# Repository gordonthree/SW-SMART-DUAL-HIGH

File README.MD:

# Dual High Side Smart Switch Node
* STM32G071 Microcontroller on board
* Dual BTS7002 Profet Smart Switches for high side loads, rated at 20 amps
* Microchip MCP2562 isolated CAN bus transceiver
* Voltage divider to monitor supply voltage
* Switch current monitoring and diagnostics
* Three position screw terminal block for CAN bus connection
* Three pos. screw terminal block for power-out, middle terminal is NC
* Heavy duty terminal block connectors for power in
* Headers for SWLINK programming and USART1 debug serial port

<IMG src="https://github.com/gordonthree/SW-SMART-DUAL-HIGH/blob/main/SW-SMART-DUAL-HIGH.png?raw=true" width=480>

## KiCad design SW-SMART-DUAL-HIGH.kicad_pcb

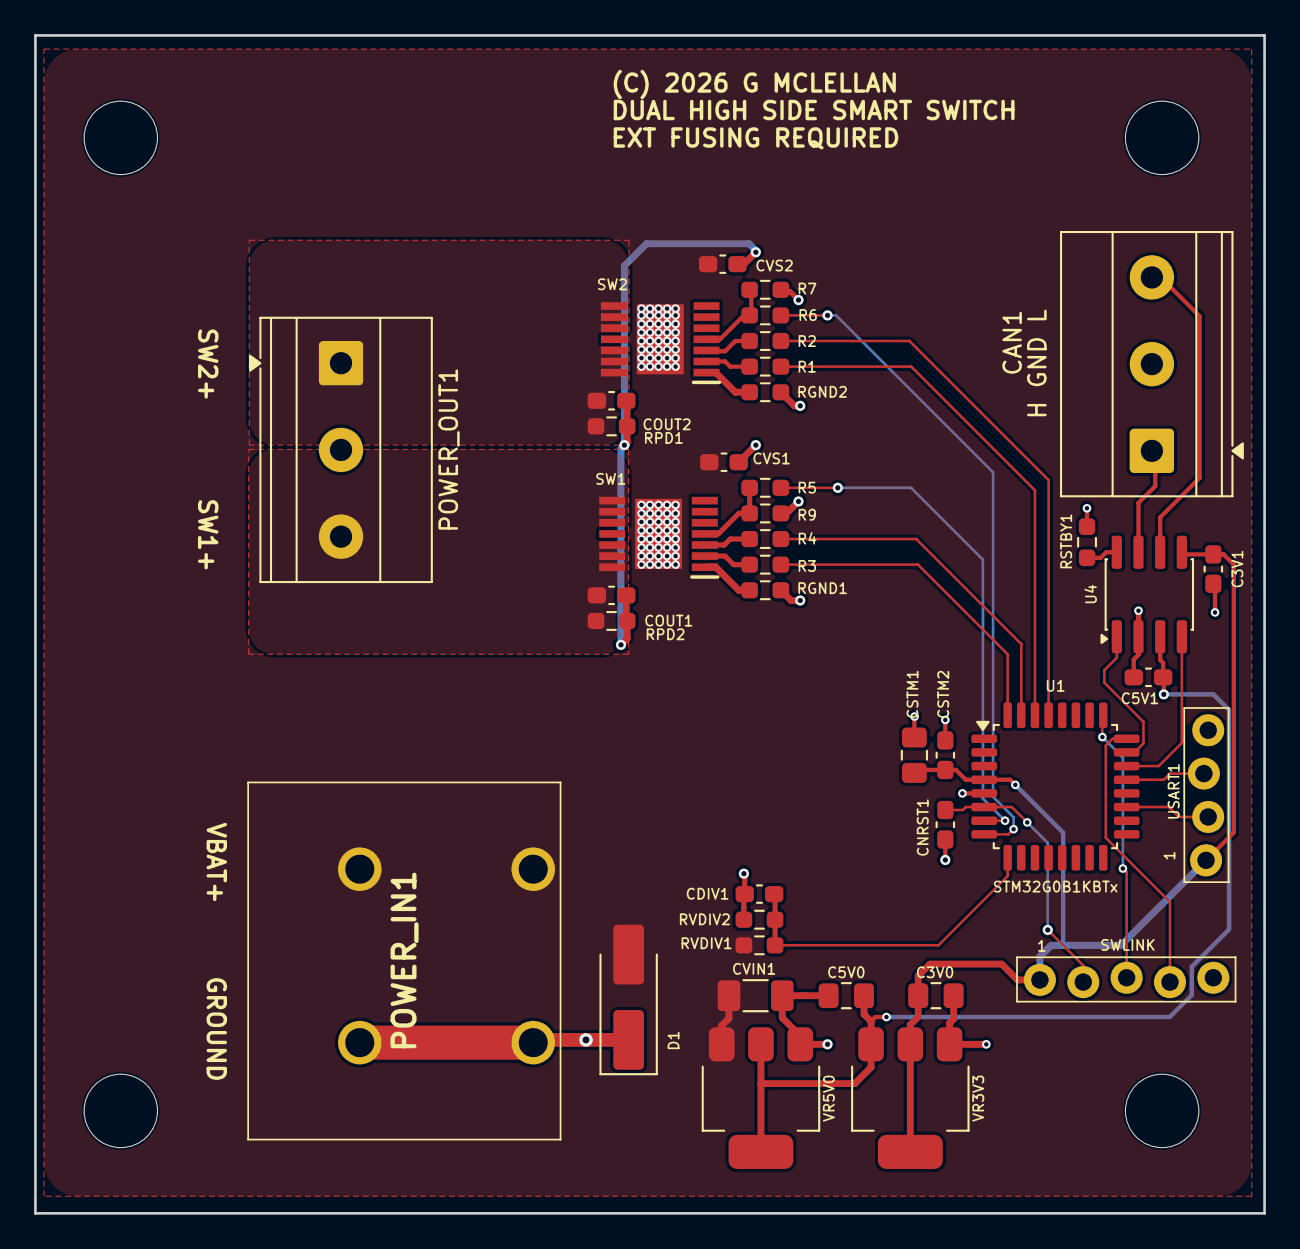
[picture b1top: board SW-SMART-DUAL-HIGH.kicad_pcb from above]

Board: 2 copper layers, 72.0 x 69.0 mm, 44 parts (0 on the bottom side), 31 nets.

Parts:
C3V0, C5V0: 10u; C_0805_2012Metric_Pad1.18x1.45mm_HandSolder
C3V1, C5V1: 100n; C_0603_1608Metric_Pad1.08x0.95mm_HandSolder
CAN1: H GND L; TerminalBlock_Phoenix_MKDS-1,5-3-5.08_1x03_P5.08mm_Horizont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
CDIV1: 100n; C_0603_1608Metric_Pad1.08x0.95mm_HandSolder
CNRST1: 100n; C_0603_1608Metric_Pad1.08x0.95mm_HandSolder
COUT1, COUT2: 10n; C_0603_1608Metric_Pad1.08x0.95mm_HandSolder
CSTM1: 4u7; C_0805_2012Metric_Pad1.18x1.45mm_HandSolder
CSTM2: 100n; C_0603_1608Metric_Pad1.08x0.95mm_HandSolder
CVIN1: 10u; C_1206_3216Metric_Pad1.33x1.80mm_HandSolder
CVS1, CVS2: 68n; C_0603_1608Metric_Pad1.08x0.95mm_HandSolder
D1: 33V; D_SMA_Handsoldering
H1, H2, H3, H4: M4 4.3mm; MountingHole_4.3mm_M4
J1: SWLINK; 1x05_P2.54mm_Locking
J2: USART1; 1x04_P2.54mm_Locking
POWER_IN1: PWRIN; VP0265840000G
POWER_OUT1: TerminalBlock_Phoenix_MKDS-1,5-3-5.08_1x03_P5.08mm_Horizont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
R1, R2, R3, R4: 4K7; R_0603_1608Metric_Pad0.98x0.95mm_HandSolder
R5, R6: 10K; R_0603_1608Metric_Pad0.98x0.95mm_HandSolder
R7, R9: 1K0; R_0603_1608Metric_Pad0.98x0.95mm_HandSolder
RGND1, RGND2: 47R; R_0603_1608Metric_Pad0.98x0.95mm_HandSolder
RPD1, RPD2: 47K; R_0603_1608Metric_Pad0.98x0.95mm_HandSolder
RSTBY1: 10K; R_0603_1608Metric_Pad0.98x0.95mm_HandSolder
RVDIV1: 4K7; R_0603_1608Metric_Pad0.98x0.95mm_HandSolder
RVDIV2: 1K0; R_0603_1608Metric_Pad0.98x0.95mm_HandSolder
SW1, SW2: BTS7002-1EPP; SOP65P600X115-15N
U1: STM32G0B1KBTx; LQFP-32_7x7mm_P0.8mm
U4: MCP2562-E-SN; SOIC-8_3.9x4.9mm_P1.27mm
VR3V3: NCV1117ST33; SOT-223-3_TabPin2
VR5V0: NCV1117ST50; SOT-223-3_TabPin2

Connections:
+3.3V: C3V0.1, C3V1.1, CSTM1.1, CSTM2.1, J1.1, J2.1, U1.4 (VDD), U4.5 (Vio), VR3V3.2 (VO)
+5V: C5V0.1, C5V1.1, U4.3 (VDD), VR3V3.3 (VI), VR5V0.2 (VO)
+12V: CVIN1.1, CVS1.1, CVS2.1, D1.2 (A2), POWER_IN1.1, POWER_IN1.2, RVDIV1.2, SW1.15 (VS), SW2.15 (VS), VR5V0.3 (VI)
/CAN1_RX: U1.22 (PA9/PA11), U4.4 (RXD)
/CAN1_TX: U1.23 (PA10/PA12), U4.1 (TXD)
/CAN_H: CAN1.1, U4.7 (CANH)
/CAN_L: CAN1.3, U4.6 (CANL)
/NRST: CNRST1.1, J1.2, U1.6 (PF2)
/SW1DEN: R4.1, U1.31 (PB7)
/SW1IN: R3.1, U1.32 (PB8)
/SW1IS: R5.1, U1.7 (PA0)
/SW1IS_PD: R5.2, R9.2, SW1.4 (IS)
/SW1OUT: COUT1.1, POWER_OUT1.3, RPD2.2, SW1.8 (OUT), SW1.9 (OUT), SW1.10 (OUT), SW1.12 (OUT), SW1.13 (OUT), SW1.14 (OUT)
/SW2DEN: R2.1, U1.29 (PB5)
/SW2IN: R1.1, U1.30 (PB6)
/SW2IS: R6.1, U1.8 (PA1)
/SW2IS_PD: R6.2, R7.2, SW2.4 (IS)
/SW2OUT: COUT2.1, POWER_OUT1.1, RPD1.2, SW2.8 (OUT), SW2.9 (OUT), SW2.10 (OUT), SW2.12 (OUT), SW2.13 (OUT), SW2.14 (OUT)
/SWCLK: J1.3, U1.25 (PA14)
/SWDIO: J1.4, U1.24 (PA13)
/USART1_RX: J2.3, U1.21 (PA10/UCPD1_DBCC2)
/USART1_TX: J2.2, U1.19 (PA9/UCPD1_DBCC1)
/VS: CDIV1.1, RVDIV1.1, RVDIV2.2, U1.9 (PA2)
GND: C3V0.2, C3V1.2, C5V0.2, C5V1.2, CAN1.2, CDIV1.2, CNRST1.2, COUT1.2, COUT2.2, CSTM1.2, CSTM2.2, CVIN1.2, CVS1.2, CVS2.2, D1.1 (A1), J1.5, J2.4, POWER_IN1.3, POWER_IN1.4, R7.1, R9.1, RGND1.2, RGND2.2, RPD1.1, RPD2.1, RSTBY1.1, RVDIV2.1, U1.5 (VSS), U4.2 (VSS), VR3V3.1 (GND), VR5V0.1 (GND)
unnamed: R4.2, SW1.3 (DEN)
unnamed: RGND1.1, SW1.1 (GND)
unnamed: R3.2, SW1.2 (IN)
unnamed: R2.2, SW2.3 (DEN)
unnamed: RGND2.1, SW2.1 (GND)
unnamed: R1.2, SW2.2 (IN)
unnamed: RSTBY1.2, U4.8 (STBY)

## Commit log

2026-01-19 rework existing design with different switch configuration
2026-01-19 lots of rework to adapt previous layout to new switch configuration
2026-01-19 add 3d rendering
2026-01-19 fix supply plane pour alignment
2026-01-19 schematic tweaks
2026-01-19 updated information

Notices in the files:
SW-SMART-DUAL-HIGH.kicad_pcb:
(C) 2026 G MCLELLAN
